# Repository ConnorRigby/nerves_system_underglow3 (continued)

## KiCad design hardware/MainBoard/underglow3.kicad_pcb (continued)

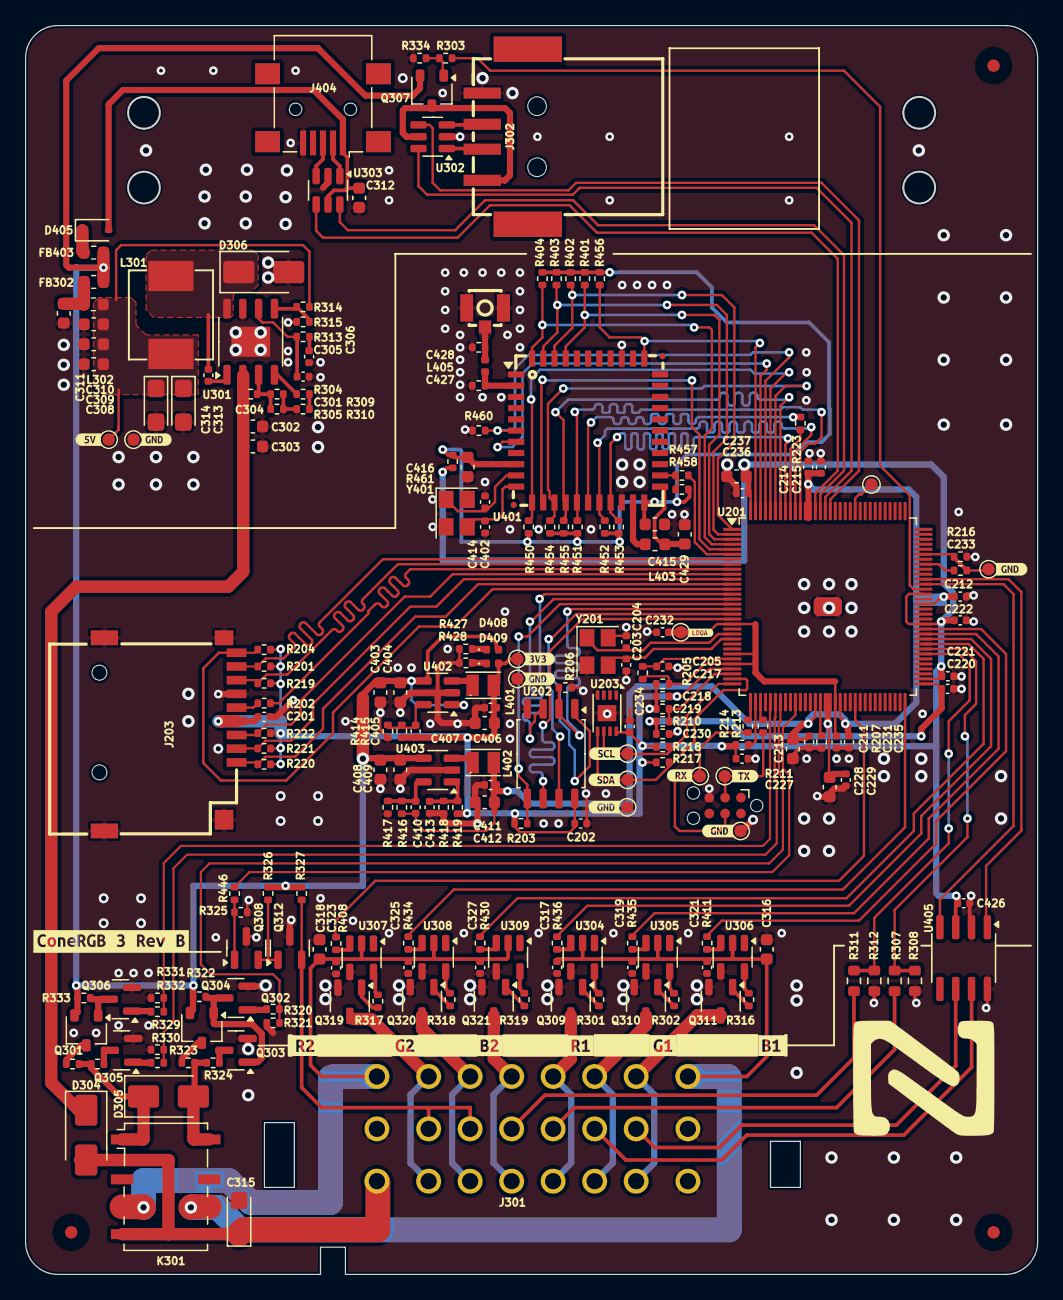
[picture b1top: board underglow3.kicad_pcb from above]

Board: 4 copper layers, 81.1 x 100.1 mm, 238 parts (0 on the bottom side), 150 nets.

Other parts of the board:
Enclosure: TestPoint_Pad_D1.0mm
TP: GND; TestPoint_Pad_D1.0mm
TP#2: GND; TestPoint_Pad_D1.0mm
U201: T113-S3; LQFP-128_14x14mm_P0.4mm
kibuzzard-65F09AC9: G***; kibuzzard-65F09AC9
kibuzzard-65F09B04: G***; kibuzzard-65F09B04
kibuzzard-65F09B16: G***; kibuzzard-65F09B16
kibuzzard-65F09B27: G***; kibuzzard-65F09B27
kibuzzard-65F09B40: G***; kibuzzard-65F09B40
kibuzzard-65F09B51: G***; kibuzzard-65F09B51
kibuzzard-65F09C6B: G***; kibuzzard-65F09C6B
kibuzzard-65F09CD2: G***; kibuzzard-65F09CD2
kibuzzard-65F09CF9: G***; kibuzzard-65F09CF9
kibuzzard-65F09D0C: G***; kibuzzard-65F09D0C
kibuzzard-65F09D1C, kibuzzard-65F09D1C#2: G***; kibuzzard-65F09D1C
kibuzzard-65FE52BD: G***; kibuzzard-65FE52BD
kibuzzard-65FE521F: G***; kibuzzard-65FE521F
kibuzzard-65FE522B, kibuzzard-65FE522B#2: G***; kibuzzard-65FE522B
kibuzzard-65FEF020: G***; kibuzzard-65FEF020
kibuzzard-65FEF408: G***; kibuzzard-65FEF408
kibuzzard-65FEF568: G***; kibuzzard-65FEF568

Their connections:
+0v9: U201.46 (VDD-SYS0), U201.51 (VDD-SYS0), U201.81 (VDD-SYS2), U201.116 (VDD-CORE0), U201.117 (VDD-CORE1); also elsewhere on the board
+1V8A: U201.89 (AVCC); also elsewhere on the board
+3V3: U201.29 (LDO-IN), U201.66 (VCC-PD), U201.77 (VCC-TVOUT), U201.83 (VCC-IO), U201.128 (VCC-PG); also elsewhere on the board
/Application/AP_WAKE_BT: U201.125 (PG13); also elsewhere on the board
/Application/BT_EN: U201.127 (PG15); also elsewhere on the board
/Application/BT_WAKE_AP: U201.126 (PG14); also elsewhere on the board
/Application/CAN0_RX: U201.85 (PB3); also elsewhere on the board
/Application/CAN0_TX: U201.86 (PB2); also elsewhere on the board
/Application/DZQ: U201.47 (DZQ); also elsewhere on the board
/Application/HCI_CTS: U201.4 (PG9); also elsewhere on the board
/Application/HCI_RTS: U201.3 (PG8); also elsewhere on the board
/Application/HCI_RX: U201.2 (PG7); also elsewhere on the board
/Application/HCI_TX: U201.1 (PG6); also elsewhere on the board
/Application/I2C_SCL: U201.32 (PE12); also elsewhere on the board
/Application/I2C_SDA: U201.31 (PE13); also elsewhere on the board
/Application/LDOA_OUT: U201.20 (VCC-PLL), U201.26 (VCC-RTC), U201.28 (LDOA-OUT), U201.50 (VDD18-DRAM); also elsewhere on the board
/Application/LDOB_OUT: U201.30 (LDOB-OUT); also elsewhere on the board
/Application/LEDC: U201.42 (PE5); also elsewhere on the board
/Application/PWM0: U201.73 (PD16); also elsewhere on the board
/Application/PWM1: U201.74 (PD17); also elsewhere on the board
/Application/PWM2: U201.75 (PD18); also elsewhere on the board
/Application/PWM3: U201.76 (PD19); also elsewhere on the board
/Application/PWM4: U201.54 (PD20); also elsewhere on the board
/Application/PWM6: U201.64 (PD9); also elsewhere on the board
/Application/RELAY_COIL_GND: U201.38 (PE9); also elsewhere on the board
/Application/RELAY_COIL_VDC: U201.37 (PE10); also elsewhere on the board
/Application/RELAY_SW: U201.39 (PE8); also elsewhere on the board
/Application/RST: U201.27 (RST); also elsewhere on the board
/Application/SDCO0_CLK: U201.9 (PF2); also elsewhere on the board
/Application/SDCO0_CMD: U201.10 (PF3); also elsewhere on the board
/Application/SDCO0_D0: U201.8 (PF1); also elsewhere on the board
/Application/SDCO0_D1: U201.7 (PF0); also elsewhere on the board
/Application/SDCO0_D2: U201.12 (PF5); also elsewhere on the board
/Application/SDCO0_D3: U201.11 (PF4); also elsewhere on the board
/Application/SD_DET: U201.13 (PF6); also elsewhere on the board
/Application/SPI0_CLK: U201.19 (PC2); also elsewhere on the board
/Application/SPI0_CS0: U201.18 (PC3); also elsewhere on the board
/Application/SPI0_HLD: U201.14 (PC7); also elsewhere on the board
/Application/SPI0_MISO: U201.16 (PC5); also elsewhere on the board
/Application/SPI0_MOSI: U201.17 (PC4); also elsewhere on the board
/Application/SPI0_WP: U201.15 (PC6); also elsewhere on the board
/Application/SUS_CLK: U201.6 (PG11); also elsewhere on the board
/Application/UART0_RX: U201.33 (PE3); also elsewhere on the board
/Application/UART0_TX: U201.35 (PE2); also elsewhere on the board
/Application/USB0_DN: U201.114 (USB0-DM); also elsewhere on the board
/Application/USB0_DP: U201.115 (USB0-DP); also elsewhere on the board
/Application/USB1_DN: U201.113 (USB1-DM); also elsewhere on the board
/Application/USB1_DP: U201.112 (USB1-DP); also elsewhere on the board
/Application/USB_SW: U201.84 (PB4); also elsewhere on the board
/Application/VCC_DRAM: U201.48 (VCC-DRAM0), U201.49 (VCC-DRAM1), U201.65 (VCC-LVDS); also elsewhere on the board
/Application/VCC_PE: U201.34 (VCC-PE); also elsewhere on the board
/Application/WIFI_CMD: U201.118 (PG1); also elsewhere on the board
/Application/WIFI_DAT0: U201.119 (PG2); also elsewhere on the board
/Application/WIFI_DAT1: U201.121 (PG3); also elsewhere on the board
/Application/WIFI_DAT2: U201.123 (PG4); also elsewhere on the board
/Application/WIFI_DAT3: U201.122 (PG5); also elsewhere on the board
/Application/WL_REG_ON: U201.124 (PG12); also elsewhere on the board
/Application/WL_WAKE_AP: U201.5 (PG10); also elsewhere on the board
/Application/XI: U201.23 (DXIN); also elsewhere on the board
/Application/XO: U201.22 (DXOUT); also elsewhere on the board
/Power/PI1_DIV: U201.72 (PD15); also elsewhere on the board
/Power/PI2_DIV: U201.71 (PD14); also elsewhere on the board
GND: TP.1, TP#2.1, U201.129 (EP); also elsewhere on the board
GNDA: U201.91 (AGND); also elsewhere on the board
unnamed 127: U201.120 (PG0); also elsewhere on the board
unnamed 128: U201.107 (VCC-TVIN); also elsewhere on the board

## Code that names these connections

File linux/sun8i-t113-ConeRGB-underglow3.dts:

// SPDX-License-Identifier: (GPL-2.0+ or MIT)
// Copyright (C) 2024 Connor Rigby <connorr@hey.com>

#include <dt-bindings/interrupt-controller/irq.h>

/dts-v1/;

#include <arm/allwinner/sun8i-t113s.dtsi>

#include <dt-bindings/gpio/gpio.h>
#include <dt-bindings/input/input.h>
#include <dt-bindings/leds/common.h>
#include <dt-bindings/pwm/pwm.h>

/ {
	model = "ConeRGB Underglow3";
	compatible = "allwinner,sun8i-t113s", "allwinner,sun8i";

	aliases {
		mmc0 = &mmc0;
		serial0 = &uart0;
		serial1 = &uart1;
		ethernet0 = &rtl8189ftv;
	};

	chosen {
		stdout-path = "serial0:115200n8";
	};

	/* board wide 5V supply directly from the USB-C socket */
	reg_vcc5v: regulator-5v {
		compatible = "regulator-fixed";
		regulator-name = "vcc-5v";
		regulator-min-microvolt = <5000000>;
		regulator-max-microvolt = <5000000>;
		regulator-always-on;
	};

	/* SY8008 DC/DC regulator on the board */
	reg_3v3: regulator-3v3 {
		compatible = "regulator-fixed";
		regulator-name = "vcc-3v3";
		regulator-min-microvolt = <3300000>;
		regulator-max-microvolt = <3300000>;
		vin-supply = <&reg_vcc5v>;
	};

	/* SY8008 DC/DC regulator on the board, also supplying VDD-SYS */
	reg_vcc_core: regulator-core {
		compatible = "regulator-fixed";
		regulator-name = "vcc-core";
		regulator-min-microvolt = <880000>;
		regulator-max-microvolt = <880000>;
		vin-supply = <&reg_vcc5v>;
	};

	reg_usb: regulator-usb {
		compatible = "regulator-fixed";
		regulator-name = "vbus-5v";
		regulator-min-microvolt = <5000000>;
		regulator-max-microvolt = <5000000>;
		gpio = <&pio 1 4 GPIO_ACTIVE_LOW>; /* PB4 */
		startup-delay-us = <1000000>; /* 1 second */
		off-on-delay-us = <1000000>; /* 1 second */
		enable-active-low;
	};

	leds {
		compatible = "gpio-leds";

		led-0 {
			color = <LED_COLOR_ID_BLUE>;
			function = LED_FUNCTION_STATUS;
			gpios = <&pio 3 22 GPIO_ACTIVE_LOW>; /* PD22 */
		};
	};

    led-controller@0 {
        compatible = "pwm-leds-multicolor";
		pinctrl-0 = <&pwm1_pd17_pins>, <&pwm2_pd18_pins>, <&pwm3_pd19_pins>;
		pinctrl-names = "default";
		multi-led {
			color = <LED_COLOR_ID_RGB>;
            function = LED_FUNCTION_INDICATOR;
            max-brightness = <100000>;
			label = "underglow:0";
			led-red {
				color = <LED_COLOR_ID_RED>;
				pwms = <&pwm 1 100000 0>;
				max-brightness = <100000>;
			};
			led-green {
				color = <LED_COLOR_ID_GREEN>;
				pwms = <&pwm 2 100000 0>;
				max-brightness = <100000>;
			};
			led-glue {
				color = <LED_COLOR_ID_BLUE>;
				pwms = <&pwm 3 100000 0>;
				max-brightness = <100000>;
			};
		};
    };

    led-controller@1 {
        compatible = "pwm-leds-multicolor";
		pinctrl-0 = <&pwm4_pd20_pins>, <&pwm6_pd9_pins>, <&pwm0_pd16_pins>;
		pinctrl-names = "default";
		multi-led {
			color = <LED_COLOR_ID_RGB>;
            function = LED_FUNCTION_INDICATOR;
            max-brightness = <100000>;
			label = "underglow:1";
			led-red {
				color = <LED_COLOR_ID_RED>;
				pwms = <&pwm 4 100000 0>;
				max-brightness = <100000>;
			};
			led-green {
				color = <LED_COLOR_ID_GREEN>;
				pwms = <&pwm 6 100000 0>;
				max-brightness = <100000>;
			};
			led-glue {
				color = <LED_COLOR_ID_BLUE>;
				pwms = <&pwm 0 100000 0>;
				max-brightness = <100000>;
			};
		};
    };

	buttons {
		compatible = "gpio-keys";
		autorepeat;

		button@1 {
			label = "User Input 1";
			linux,code = <KEY_A>;
			gpios = <&pio 3 15 0>; /* PD15 */
		};

		button@2 {
			label = "User Input 2";
			linux,code = <KEY_B>;
			gpios = <&pio 3 14 0>; /* PD14 */
		};
	};

	wifi_pwrseq: wifi-pwrseq {
		compatible = "mmc-pwrseq-simple";
		reset-gpios = <&pio 6 12 GPIO_ACTIVE_LOW>; /* PG12 */
		post-power-on-delay-ms = <200>;
	};
};

&dcxo {
	clock-frequency = <24000000>;
};

&cpu0 {
	cpu-supply = <&reg_vcc_core>;
	clock-frequency = <1200000000>;
};

&cpu1 {
	cpu-supply = <&reg_vcc_core>;
	clock-frequency = <1200000000>;
};

&wdt {
	status = "okay";
};

&pio {
	vcc-pb-supply = <&reg_3v3>;
	vcc-pc-supply = <&reg_3v3>;
	vcc-pd-supply = <&reg_3v3>;
	vcc-pe-supply = <&reg_3v3>;
	vcc-pf-supply = <&reg_3v3>;
	vcc-pg-supply = <&reg_3v3>;

	uart0_pe2_pins: uart0-pe2-pins {
		pins = "PE2", "PE3";
		function = "uart0";
	};

	i2c2_pe12_pins: i2c2-pe12-pins {
		pins = "PE12", "PE13";
		function = "i2c2";
	};

	pwm0_pd16_pins: pwm0-pd16-pins {
		pins = "PD16";
		function = "pwm0";
	};

	pwm1_pd17_pins: pwm1-pd16-pins {
		pins = "PD17";
		function = "pwm1";
	};

	pwm2_pd18_pins: pwm2-pd18-pins {
		pins = "PD18";
		function = "pwm2";
	};

	pwm3_pd19_pins: pwm2-pd19-pins {
		pins = "PD19";
		function = "pwm3";
	};

	pwm4_pd20_pins: pwm4-pd20-pins {
		pins = "PD20";
		function = "pwm4";
	};

	/omit-if-no-ref/
	pwm5_pd21_pins: pwm5-pd21-pins {
		pins = "PD21";
		function = "pwm5";
	};

	pwm6_pd9_pins: pwm6-pd9-pins {
		pins = "PD9";
		function = "pwm6";
	};

	/omit-if-no-ref/
	pwm7_pd22_pins: pwm7-pd22-pins {
		pins = "PD22";
		function = "pwm7";
	};

	ledc_pe5_pin: ledc-pe5-pin {
		pins = "PE5";
		function = "ledc";
	};

	spi0_cs0_pc_pin: spi0-cs0-pc-pin {
		pins = "PC3";
		function = "spi0";
	};
};

&pwm {
	status = "okay";
};

&ledc {
	pinctrl-0 = <&ledc_pe5_pin>;
	pinctrl-names = "default";
	status = "okay";
	allwinner,pixel-format = "grb";
	allwinner,t0h-ns = "320";
	allwinner,t0l-ns = "800";
	allwinner,t1h-ns = "840";
	allwinner,t1l-ns = "400";
	allwinner,treset-ns = "300000";
	label = "underglow:ledc";
};

&uart0 {
	pinctrl-0 = <&uart0_pe2_pins>;
	pinctrl-names = "default";
	status = "okay";
};

&uart1 {
	uart-has-rtscts;
	pinctrl-0 = <&uart1_pg6_pins>, <&uart1_pg8_rts_cts_pins>;
	pinctrl-names = "default";
	status = "okay";

	bluetooth {
		compatible = "realtek,rtl8723bs-bt";
		device-wake-gpios = <&pio 6 13 GPIO_ACTIVE_HIGH>; /* PG13 */
		host-wake-gpios =  <&pio 6 14 GPIO_ACTIVE_HIGH>; /* PG14 */
		enable-gpios = <&pio 6 15 GPIO_ACTIVE_HIGH>; /* PG15 */
		max-speed = <115200>;
		// max-speed = <1500000>;
		status = "okay";
	};
};

&i2c2 {
	pinctrl-0 = <&i2c2_pe12_pins>;
	pinctrl-names = "default";
	status = "okay";
	clock-frequency = <62000>;
};

&mmc0 {
	pinctrl-0 = <&mmc0_pins>;
	pinctrl-names = "default";
	vmmc-supply = <&reg_3v3>;
	cd-gpios = <&pio 5 6 GPIO_ACTIVE_LOW>;
	disable-wp;
	bus-width = <4>;
	status = "okay";
};

&mmc1 {
	pinctrl-0 = <&mmc1_pins>;
	pinctrl-names = "default";

	/* SDIO to WiFi module */
	vmmc-supply = <&reg_3v3>;
	mmc-pwrseq = <&wifi_pwrseq>;
	bus-width = <4>;
	non-removable;
	status = "okay";

	rtl8189ftv: wifi@1 {
		reg = <1>;
		interrupt-parent = <&pio>;
		interrupts = <6 10 IRQ_TYPE_LEVEL_LOW>; /* PG10 = WL_WAKE_AP */
		interrupt-names = "host-wake";
	};
};

&usb_otg {
	dr_mode = "peripheral";
	status = "okay";
};

&usbphy {
	usb1_vbus-supply = <&reg_usb>;
	status = "okay";
};

&ehci1 {
	status = "okay";
};

&ohci1 {
	status = "okay";
};

&can0 {
	pinctrl-names = "default";
	pinctrl-0 = <&can0_pins>;
	status = "okay";
};

&spi0 {
	status = "disabled";
};

&mixer0 {
	status = "disabled";
};

&tcon_top {
	status = "disabled";
};

&tcon_lcd0 {
	status = "disabled";
};

&crypto {
	status = "okay";
};

#include "sun8i-t113-ledc.dtsi"

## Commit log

2024-02-29 enable CAN and LEDC
2024-03-20 enable PWM
2024-03-21 update uboot to 2024.04-rc4
2024-03-21 enable pwm7
2024-03-21 cleanup unused patches
2024-03-23 initial bringup release
2024-03-23 v0.1.0 release
2024-03-23 hex publish
2024-03-23 Initial hardware release
2024-03-23 Github pages
2024-03-23 Add docs index
2024-03-30 Bringup updates
    * Enable ledc
    * Enable temporary rtl wifi driver
    * Enable kernel bluetooth
    * Enable ipv6
2024-03-30 v0.2.0 release
2024-07-15 Update Linux, Uboot add python and bluez
2024-07-15 Add bluetoothd config file to dbus init
2024-07-21 Bump BlueZ
2024-07-21 Remove unused sun6i rtc driver
2024-07-24 v0.3.0 release
